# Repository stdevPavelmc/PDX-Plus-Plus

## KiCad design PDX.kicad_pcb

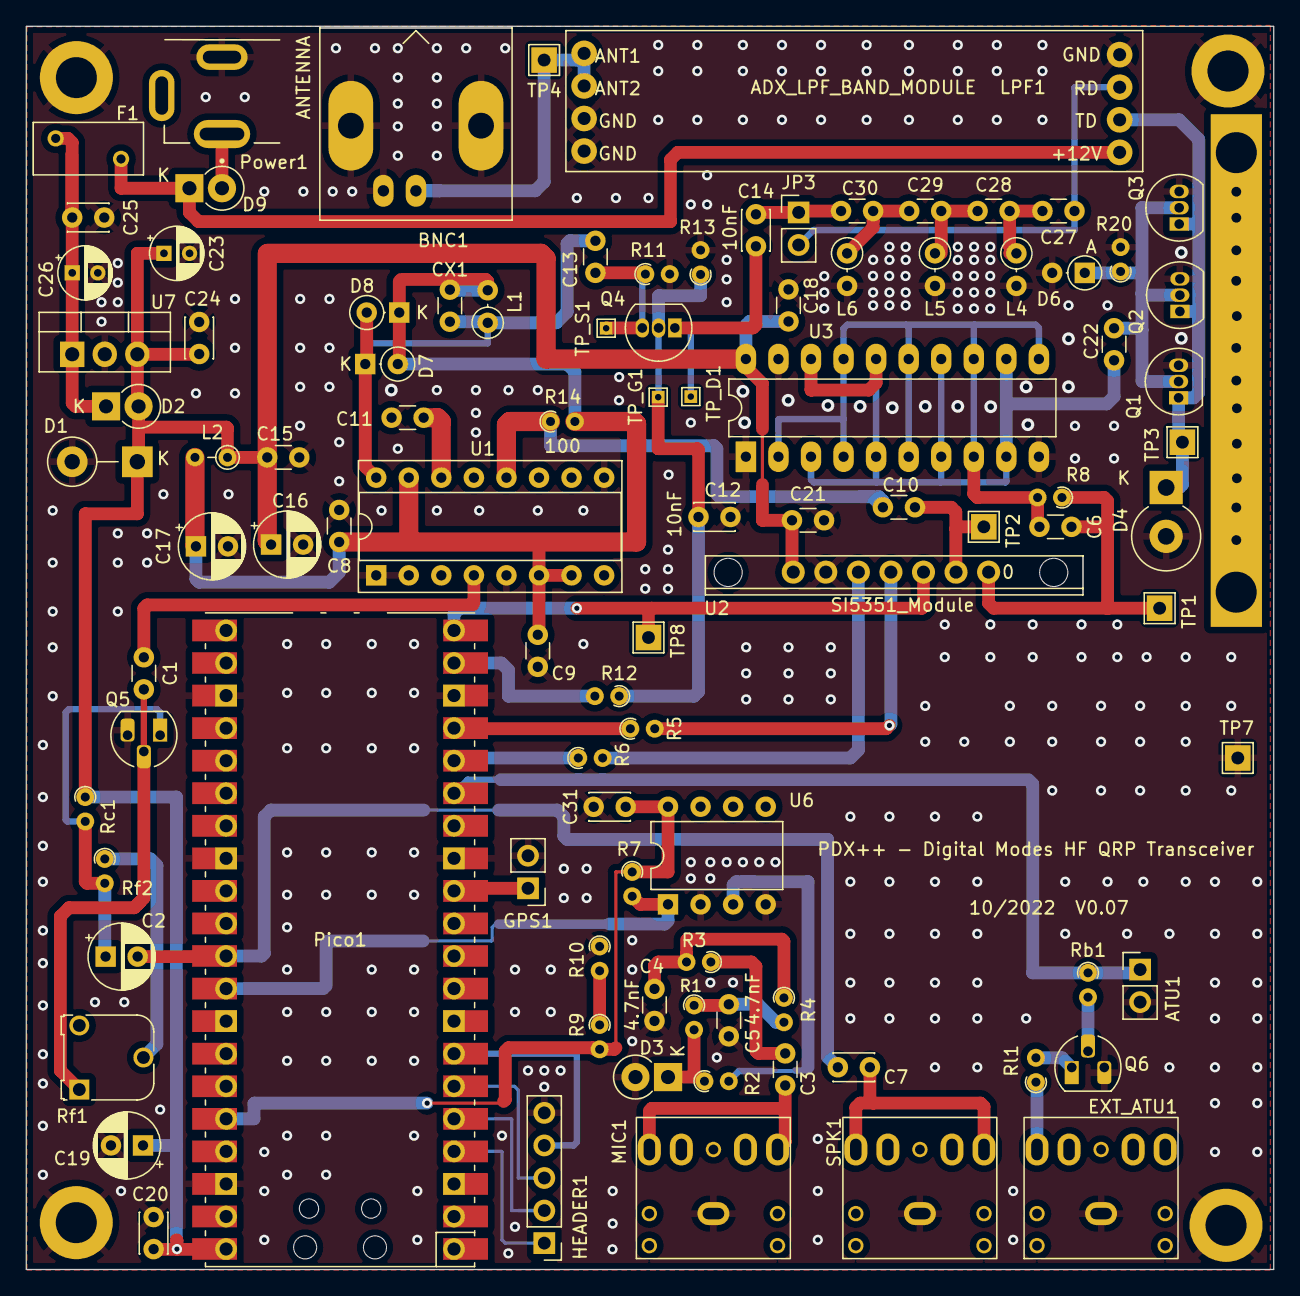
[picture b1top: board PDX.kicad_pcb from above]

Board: 2 copper layers, 97.3 x 97.0 mm, 104 parts (0 on the bottom side), 54 nets.

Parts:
ATU1: Conn_01x02; PinHeader_1x02_P2.54mm_Vertical
BNC1: BNC; BNC_Amphenol_B6252HB-NPP3G-50_Horizontal
C1, C3, C8, C9, C10, C11, C15, C18, C21, C22: 100nF; C_Disc_D3.0mm_W1.6mm_P2.50mm
C2, C19: 10uF; CP_Radial_D5.0mm_P2.50mm
C4, C5: 4.7nF; C_Disc_D3.0mm_W1.6mm_P2.50mm
C6: 100pF; C_Disc_D3.0mm_W1.6mm_P2.50mm
C7: 470nF; C_Disc_D3.0mm_W2.0mm_P2.50mm
C12, C14: 10nF; C_Disc_D3.0mm_W2.0mm_P2.50mm
C13: 680pF / 620pF; C_Disc_D3.0mm_W1.6mm_P2.50mm
C16: 100uF/16V; CP_Radial_D5.0mm_P2.50mm
C17: 10uF/16V; CP_Radial_D5.0mm_P2.50mm
C20, C24, C25, C31: 100nF; C_Disc_D3.0mm_W2.0mm_P2.50mm
C23: 10uF/16V; CP_Radial_D4.0mm_P2.00mm
C26: 100uF/16V; CP_Radial_D4.0mm_P2.00mm
C27, C30: 2.2nF; C_Disc_D3.0mm_W1.6mm_P2.50mm
C28, C29: 820; C_Disc_D3.0mm_W1.6mm_P2.50mm
CX1: C_Disc_D3.0mm_W1.6mm_P2.50mm
D1: 5.6V 5W; D_DO-15_P5.08mm_Vertical_KathodeUp
D2: 1N4001; D_DO-41_SOD81_P2.54mm_Vertical_KathodeUp
D3: 1N581X; D_DO-41_SOD81_P2.54mm_Vertical_KathodeUp
D4: 47v 5W; D_DO-201_P3.81mm_Vertical_KathodeUp
D6: 1N4148; D_DO-35_SOD27_P2.54mm_Vertical_AnodeUp
D7, D8: 1N4148; D_DO-35_SOD27_P2.54mm_Vertical_KathodeUp
D9: 1N5817; D_DO-41_SOD81_P2.54mm_Vertical_KathodeUp
EXT_ATU1: EXT_ATU; PJ-307_Modded
F1: 1A; Fuse_BelFuse_0ZRE0005FF_L8.3mm_W3.8mm
GPS1: Conn_01x02; PinHeader_1x02_P2.54mm_Vertical
H1, H2, H3, H4: MountingHole_Pad; MountingHole_3.2mm_M3_ISO7380_Pad
HEADER1: Conn_01x05; PinHeader_1x05_P2.54mm_Vertical
HS1: Heatsink_Pad; ThermalPad_Final
JP3: Filter-Skip; PinHeader_1x02_P2.54mm_Vertical
L1: 1uH; L_Axial_L5.3mm_D2.2mm_P2.54mm_Vertical_Vishay_IM-1
L2: 100uH; R_Axial_DIN0204_L3.6mm_D1.6mm_P2.54mm_Vertical
L4, L5, L6: 2.2uH; L_Axial_L5.3mm_D2.2mm_P2.54mm_Vertical_Vishay_IM-1
LPF1: ADX_LPF_BAND_MODULE; uSDX_LPF_Band_Module
MIC1: MIC; PJ-307_Modded
Pico1: Pico; RPi_Pico_SMD_TH
Power1: DC-005 (Barrel Jack); XKB_DC-005-5A-2.0
Q1, Q2, Q3, Q4: BS170; TO-92_Inline
Q5, Q6: BC547; TO-92_HandSolder
R1, R2: 5.1k; R_Axial_DIN0204_L3.6mm_D1.6mm_P1.90mm_Vertical
R3, R4, R7, R9, R10, R13: 10k; R_Axial_DIN0204_L3.6mm_D1.6mm_P1.90mm_Vertical
R5, R6, R12: 330; R_Axial_DIN0204_L3.6mm_D1.6mm_P1.90mm_Vertical
R8, R14: 100; R_Axial_DIN0204_L3.6mm_D1.6mm_P1.90mm_Vertical
R11: 1k; R_Axial_DIN0204_L3.6mm_D1.6mm_P1.90mm_Vertical
R20: 2.7k; R_Axial_DIN0204_L3.6mm_D1.6mm_P1.90mm_Vertical
Rb1: 1k; R_Axial_DIN0204_L3.6mm_D1.6mm_P1.90mm_Vertical
Rc1: 4.7k; R_Axial_DIN0204_L3.6mm_D1.6mm_P1.90mm_Vertical
Rf1: 500k (keep ~10k); Potentiometer_Runtron_RM-065_Vertical
Rf2: 4.7k; R_Axial_DIN0204_L3.6mm_D1.6mm_P1.90mm_Vertical
Rl1: 470; R_Axial_DIN0204_L3.6mm_D1.6mm_P1.90mm_Vertical
S1, S2: MountingHole; MountingHole_2.2mm_M2
SPK1: SPEAKER; PJ-307_Modded
TP1: CLK0; TestPoint_THTPad_2.0x2.0mm_Drill1.0mm
TP2: CLK1; TestPoint_THTPad_2.0x2.0mm_Drill1.0mm
TP3, TP4: TestPoint; TestPoint_THTPad_2.0x2.0mm_Drill1.0mm
TP7: GND; TestPoint_THTPad_2.0x2.0mm_Drill1.0mm
TP8: CAL; TestPoint_THTPad_2.0x2.0mm_Drill1.0mm
TP_D1: TestPoint_THTPad_1.0x1.0mm_Drill0.5mm
TP_G1: TestPoint_THTPad_1.0x1.0mm_Drill0.5mm
TP_S1: TestPoint_THTPad_1.0x1.0mm_Drill0.5mm
U1: CD2003GB_GP; DIP-16_W7.62mm_Socket
U2: SI5351_Module; SI5351 Module_Vertical
U3: 74ACT244; DIP-20_W7.62mm_LongPads
U6: LM393; DIP-8_W7.62mm
U7: CDIL_7805_TO220; TO-220-3_Vertical

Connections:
+3.3V: C31.1, Pico1.36 (3V3), R7.1, R9.2, U6.8 (V+)
+5V: C15.1, C16.1, C18.2, C19.1, C20.2, C21.1, C23.1, C24.1, D1.1 (K), D2.2 (A), L2.1, Pico1.40 (VBUS), Rc1.1, U2.1 (VIN), U3.20 (VCC), U7.3 (VO)
FSK: Pico1.32 (GPIO27_ADC1), R7.2, U6.1
GNDPWR: ATU1.2, BNC1.2 (Ext), C4.2, C5.2, C8.1, C9.1, C11.1, C12.2, C15.2, C16.2, C17.2, C18.1, C19.2, C20.1, C21.2, C23.2, C24.2, C25.2, C26.2, C31.2, D1.2 (A), D3.2 (A), D4.2 (A), D6.2 (A), EXT_ATU1.S, GPS1.2, H1.1, H2.1, H3.1, H4.1, HEADER1.5, L4.2, L5.2, L6.2, LPF1.4 (GND), LPF1.7 (GND), LPF1.8 (GND), MIC1.S, Pico1.13 (GND), Pico1.18 (GND), Pico1.23 (GND), Pico1.28 (GND), Pico1.38 (GND), Power1.2, Q1.3 (S), Q2.3 (S), Q3.3 (S), Q5.3 (E), Q6.3 (E), R10.1, R11.2, R13.2, R20.2, SPK1.S, TP7.1, U1.1 (FM_RF_IN), U1.2 (GND_IN), U1.5 (AGC), U1.9 (GND_OUT), U2.2 (GND), U3.1 (OEa), U3.10 (GND), U3.19 (OEb), U6.2 (-), U6.4 (V-), U7.2 (GND)
unnamed: ATU1.1, Pico1.15 (GPIO11), Rb1.1
unnamed: BNC1.1 (In), LPF1.5 (ANT1), LPF1.6 (ANT2), TP4.1
unnamed: C1.2, Q5.2 (B), Rf1.1
unnamed: C2.1, Q5.1 (C), Rc1.2, Rf2.2
unnamed: C3.1, R3.1
unnamed: C3.2, MIC1.R, MIC1.T
unnamed: C4.1, R3.2, R4.1
unnamed: C5.1, R1.1, R4.2
unnamed: C6.1, R8.1, TP1.1, U2.7 (SO)
unnamed: C6.2, R8.2, U3.2 (I0a), U3.4 (I1a), U3.6 (I2a), U3.8 (I3a), U3.11 (I0b), U3.13 (I1b), U3.15 (I2b), U3.17 (I3b)
unnamed: C7.1, SPK1.R, SPK1.T
unnamed: C10.1, R14.1, U1.12 (AM_OSC)
unnamed: C11.2, U1.14 (FM/AM_SW)
unnamed: C13.1, Q4.3 (S), R11.1, TP_S1.1
unnamed: C13.2, CX1.1, D7.1 (K), D8.2 (A), L1.1, U1.16 (AM_RF_IN)
unnamed: C14.1, Q4.1 (D), TP_D1.1
unnamed: C14.2, C30.2, JP3.1 (A)
unnamed: C8.2, C9.2, C17.1, CX1.2, D7.2 (A), D8.1 (K), L1.2, L2.2, R14.2, U1.6 (VCC), U1.7 (AM_IF), U1.15 (FM_TUNER)
unnamed: C22.1, D6.1 (K), Q1.2 (G), Q2.2 (G), Q3.2 (G), R20.1
unnamed: C22.2, U3.3 (O3b), U3.5 (O2b), U3.7 (O1b), U3.9 (O0b), U3.12 (O3a), U3.14 (O2a), U3.16 (O1a), U3.18 (O0a)
unnamed: C25.1, C26.1, D2.1 (K), F1.2, U7.1 (VI)
unnamed: C27.2, C28.1, L4.1
unnamed: C28.2, C29.1, L5.1
unnamed: C29.2, C30.1, L6.1
unnamed: D3.1 (K), R1.2, R2.1
unnamed: D9.1 (K), F1.1, LPF1.1 (+12V)
unnamed: D9.2 (A), Power1.1
unnamed: EXT_ATU1.R, Rl1.1
unnamed: GPS1.1, Pico1.12 (GPIO9)
unnamed: Pico1.19 (GPIO14), R12.2
unnamed: Pico1.20 (GPIO15), TP8.1, U2.5 (S2)
unnamed: Q6.1 (C), Rl1.2
unnamed: Q6.2 (B), Rb1.2
unnamed: R2.2, U6.3 (+)
unnamed: R5.2, U2.4 (SCL)
unnamed: R6.2, U2.3 (SDA)
unnamed: R9.1, R10.2
unnamed: Rf1.2, Rf2.1
RX: C27.1, JP3.2 (B), LPF1.3 (RD)
RXSW: C12.1, Q4.2 (G), R12.1, R13.1, TP_G1.1
RX_AUDIO: C1.1, U1.4 (AM_MIX)
RX_OSC: C10.2, TP2.1, U2.6 (S1)
SCL: Pico1.17 (GPIO13), R5.1
SDA: Pico1.16 (GPIO12), R6.1
SW1: HEADER1.1, Pico1.4 (GPIO2)
SW2: HEADER1.2, Pico1.5 (GPIO3)
SW3: HEADER1.3, Pico1.6 (GPIO4)
TD_IN: D4.1 (K), LPF1.2 (TD), Q1.1 (D), Q2.1 (D), Q3.1 (D), TP3.1
TO_ADC: C2.2, C7.2, Pico1.31 (GPIO26_ADC0)
TXLED: HEADER1.4, Pico1.7 (GPIO5)
